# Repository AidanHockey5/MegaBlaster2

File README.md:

# Mega Blaster 2

Demo video can be found here: https://www.youtube.com/watch?v=4sKwGWfikdc

[Instruction Manual](https://github.com/AidanHockey5/MegaBlaster2/raw/master/man/MegaBlaster2InstructionManual.pdf)

[Store Link](https://www.aidanlawrence.com/product/mega-blaster-2/)

[Discord Link](https://discord.gg/M2skqkZhw2)

This project contains the source material for the Mega Blaster 2, a hardware Sega Genesis/Mega Drive video game music (VGM) player that utilizes the real sound chips. Play any Genesis track on-demand with brilliant sound quality on the actual YM2612/YM3438 and SN76489 PSG synthesizer chips that were found in the real Genesis consoles(1). The Mega Blaster 2 is compatible with both .vgm and .vgz files and can support both the YM2612 and YM3438 simply by changing the DIP switch values. This unit does not use any emulated sound - these are the real chips playing back logged data from the vgm files. 

# VGM Files

VGM files are logged datasets of the data that would have been sent to the real sound chips of whatever console or arcade machine was being sampled. The Mega Blaster 2 simply reads-in this data and sends it to the sound chips at the exact rate specified in the VGM spec, accurately recreating the original sound.

You can find Genesis VGM files here: https://project2612.org/list.php

You can find more VGM files here: https://vgmrips.net/packs/

Please make sure to remove any non-vgm/vgz files before adding them to your Mega Blaster 2's SD card, such as album art images, playlist files, and text files.

# VGM vs. VGZ

VGZ files are gzip compressed versions of VGM files. The Mega Blaster 2 is capable of automatically decompressing these vgz files on-the-fly at a slight performance penalty. If you'd like faster load times for each track, consider decompressing the VGZ files in advance by opening them with a program like [7zip](https://www.7-zip.org/)
The Mega Blaster 2 does not require file extensions in order to operate as it will verify files based on their internal headers.

# Building Your Own Unit

Here are some quick tips for building your own board.

1) You can find an interactive Bill of Materials (BOM) within the `schematic->bom` folder. Open the HTML file in any browser for an easy-to-use part position guide.
2) I use [KiCAD](https://kicad.org/) as my EDA suite.
4) I buy most of my components from [LCSC](https://lcsc.com/). I buy my PCBs from [JLCPCB](https://jlcpcb.com/). If you buy your PCBs from JLCPCB, you can often get a shipping discount on your LCSC parts order.
5) You will need an [Atmel ICE](https://www.microchip.com/DevelopmentTools/ProductDetails/ATATMEL-ICE) or [Jlink](https://www.segger.com/products/debug-probes/j-link/) to flash the bootloader. Once you have flashed the bootloader, all subsequent programming can be done via the on-board USB port. A cheaper option would be to grab a [Jlink EDU Mini](https://shop-us.segger.com/J_Link_EDU_mini_p/8.08.91.htm) as they feature the full functionality of a professional Jlink Unit with the stipulation that it is ONLY to be used for educational purposes. I personally use an Atmel ICE unit. You can find the bootloader bin file in the `bootloader` folder of the repository. [You can find an example of me programming the bootloader using Microchip Studio here.](https://youtu.be/FjPftGuLnGg?t=9259)
6) Once you've flashed the bootloader, you can drag the [.uf2 firmware file found on the releases page](https://github.com/AidanHockey5/MegaBlaster2/releases) on to the "drive" that pops up on your computer, or build from source. If you can't see any "drive," make sure the bootloader mentioned above is flashed correctly, then try double-tapping the RESET button. 
7) If your OS reports a USB fault, you may have a short somewhere on your USB IO lines, power lines, or your 32.768KHz crystal is not hooked up correctly.
8) I use [Visual Studio Code](https://code.visualstudio.com/) with the [PlatformIO](https://platformio.org/install/ide?install=vscode) extension.
9) Make sure your SN76489 PSG chip is orientated correctly. On this board, the PSG is upside-down relative to the rest of the board. The Flash IC is also upside-down. This was done for routing purposes. A small star on the silk-screen indicates the pin-1 position of every IC.
10) For general usage instructions, [please refer to the manual](https://github.com/AidanHockey5/MegaBlaster2/raw/master/man/MegaBlaster2InstructionManual.pdf).

# Reporting Bugs

As you can imagine, this is quite a complex project. There are bound to be bugs to squish, so if you happen to find any, [please report them over on the issues page](https://github.com/AidanHockey5/MegaBlaster2/issues) so I can tkae a look at them! Please try to document the steps it takes to recreate the bug if you happen to know them.

# Schematic

# License
The source code to this project is licensed under the AGPL 3.0 license.

The printed circuit board design files for the Mega Blaster 2, including it’s schematic, gerber files, KiCAD files, bill-of-materials, and 3D models are licensed under the Creative Commons Attribution-NonCommercial-ShareAlike 4.0 license.

You are permitted to build your own Mega Blaster 2 units for personal use. You are not permitted to sell said units.

(1) Pedantic note: Discrete YM2612 ICs were indeed included on some models of the Genesis, but the SN76489 PSG and YM3438 were found baked into ASIC chips on the actual consoles. The PSG's noise is slightly different on the ASIC version.

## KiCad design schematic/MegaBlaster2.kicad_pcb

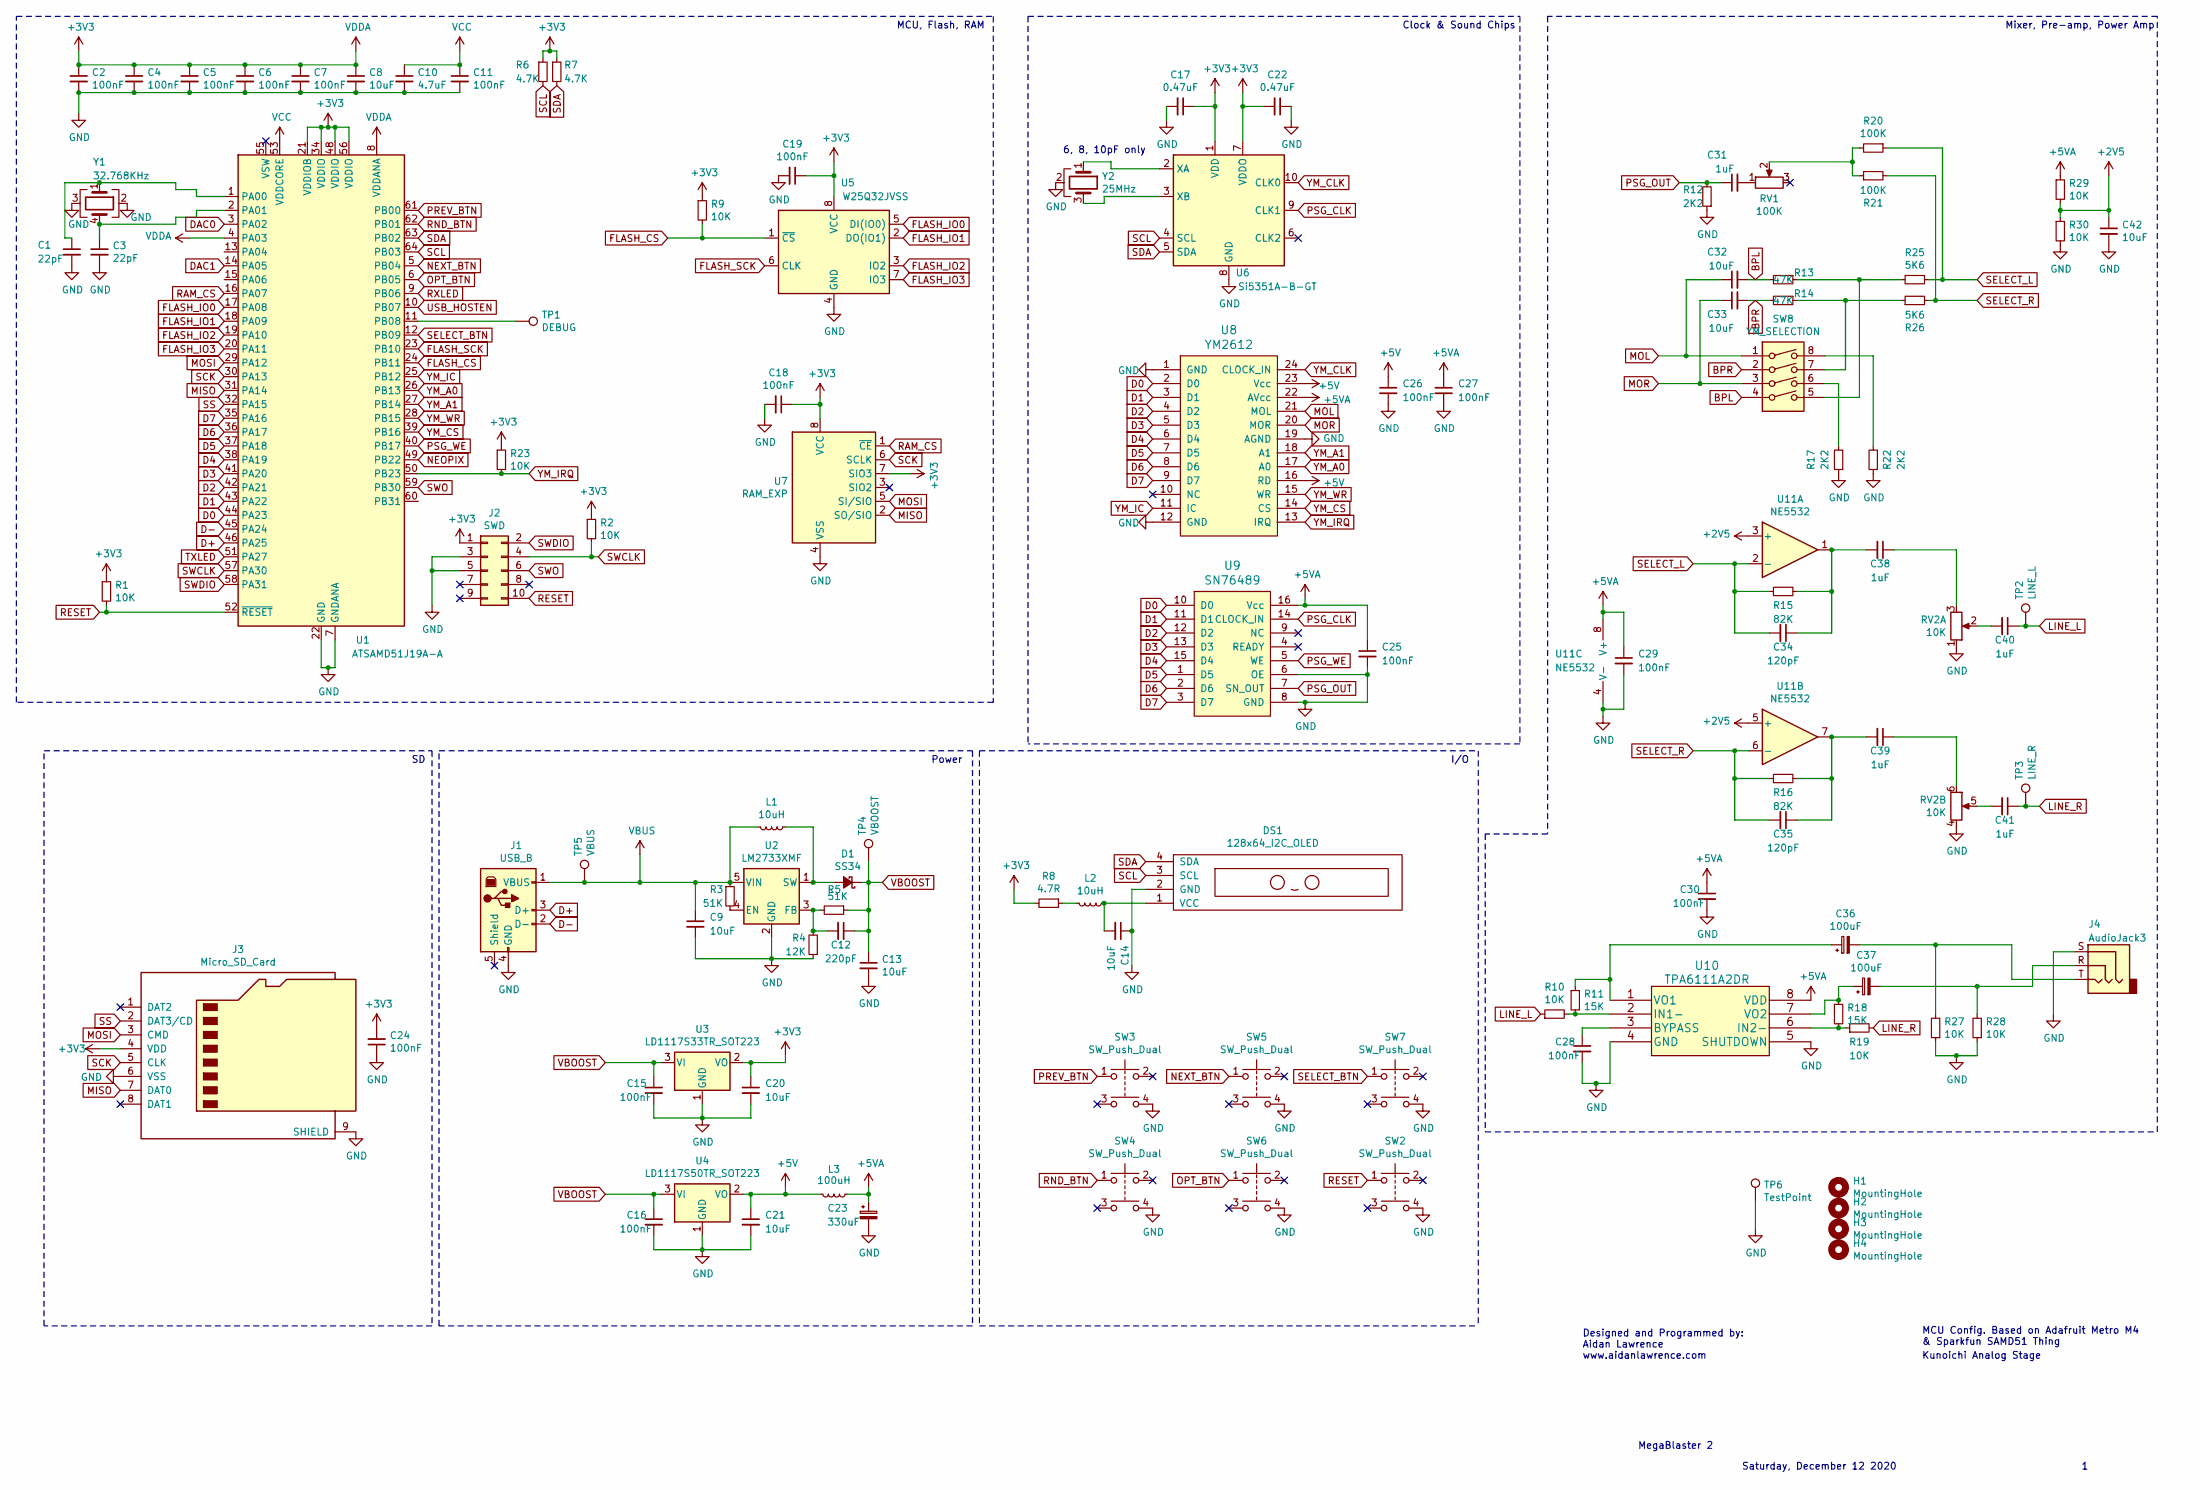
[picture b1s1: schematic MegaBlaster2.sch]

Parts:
C1, C3: 22pF; C_0603_1608Metric
C2, C4, C5, C6, C7, C11, C15, C16, C18, C19, C24, C25, C26, C27, C28, C29, C30: 100nF; C_0805_2012Metric
C8, C9, C13, C14, C20, C21, C32, C33, C42: 10uF; C_1206_3216Metric
C10: 4.7uF; C_0805_2012Metric
C12: 220pF; C_0603_1608Metric
C17, C22: 0.47uF; C_0805_2012Metric
C23: 330uF; CP_Elec_8x10
C31, C38, C39, C40, C41: 1uF; C_0805_2012Metric
C34, C35: 120pF; C_0603_1608Metric
C36, C37: 100uF; CP_Elec_6.3x7.7
D1: SS34; D_SMA
DS1: 128x64_I2C_OLED; oled_128x64
H1, H2, H3, H4: MountingHole; MountingHole_3.2mm_M3
J1: USB_B; USB_B_Lumberg_2411_02_Horizontal
J2: SWD; PinHeader_2x05_P1.27mm_Vertical
J3: Micro_SD_Card; SOFNG_TF_15x15_PUSH_PUSH
J4: AudioJack3; SWITCHCRAFT_35RAPC4BHN2
L1, L2: 10uH; L_4x4
L3: 100uH; 6x6Inductor
R1, R2, R9, R10, R19, R23, R27, R28, R29, R30: 10K; R_0805_2012Metric
R3, R5: 51K; R_0805_2012Metric
R4: 12K; R_0805_2012Metric
R6, R7: 4.7K; R_0805_2012Metric
R8: 4.7R; R_0805_2012Metric
R11, R18: 15K; R_0805_2012Metric
R12, R17, R22: 2K2; R_0805_2012Metric
R13, R14: 47K; R_0805_2012Metric
R15, R16: 82K; R_0805_2012Metric
R20, R21: 100K; R_0805_2012Metric
R25, R26: 5K6; R_0805_2012Metric
RV1: 100K; 3362P-1-103LF
RV2: 10K; Potentiometer_Alps_RK097_Dual_Horizontal
SW2, SW3, SW4, SW5, SW6, SW7: SW_Push_Dual; SW_TH_Tactile_Omron_B3F-10xx
SW8: YM_SELECTION; SW_DIP_SPSTx04_Slide_9.78x12.34mm_W7.62mm_P2.54mm
TP1: DEBUG; TestPoint_Pad_D2.0mm
TP2: LINE_L; TestPoint_Pad_D2.0mm
TP3: LINE_R; TestPoint_Pad_D2.0mm
TP4: VBOOST; TestPoint_Pad_D2.0mm
TP5: VBUS; TestPoint_Pad_D2.0mm
TP6: TestPoint; TestPoint_Pad_2.0x2.0mm
U1: ATSAMD51J19A-A; TQFP-64_10x10mm_P0.5mm
U2: LM2733XMF; SOT-23-5
U3: LD1117S33TR_SOT223; SOT-223-3_TabPin2
U4: LD1117S50TR_SOT223; SOT-223-3_TabPin2
U5: W25Q32JVSS; SOIC-8_5.23x5.23mm_P1.27mm
U6: Si5351A-B-GT; MSOP-10_3x3mm_P0.5mm
U7: RAM_EXP; SOIC-8_3.9x4.9mm_P1.27mm
U8: YM2612; DIP-24_W15.24mm_Socket
U9: SN76489; DIP-16_W7.62mm_Socket
U10: TPA6111A2DR; SOIC-8_3.9x4.9mm_P1.27mm
U11: NE5532; SOIC-8_3.9x4.9mm_P1.27mm
Y1: 32.768KHz; Crystal_SMD_SeikoEpson_MC306-4Pin_8.0x3.2mm
Y2: 25MHz; Crystal_SMD_3225-4Pin_3.2x2.5mm

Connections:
+2V5: C42.1, R29.2, R30.1, U11.3 (+), U11.5 (+)
+3V3: C2.1, C4.1, C5.1, C6.1, C7.1, C8.1, C17.1, C18.1, C19.1, C20.1, C22.2, C24.2, J2.1, J3.4 (VDD), R1.1, R2.1, R6.1, R7.1, R8.2, R9.1, R23.1, U1.4 (PA03), U1.8 (VDDANA), U1.21 (VDDIOB), U1.34 (VDDIO), U1.48 (VDDIO), U1.56 (VDDIO), U3.2 (VO), U5.8 (VCC), U6.1 (VDD), U6.7 (VDDO), U7.7 (SIO3), U7.8 (VCC)
+5V: C21.1, C26.1, L3.2, U4.2 (VO), U8.16 (RD), U8.23 (Vcc)
+5VA: C23.1, C25.1, C27.1, C29.1, C30.1, L3.1, R29.1, U8.22 (AVcc), U9.16 (Vcc), U10.8 (VDD), U11.8 (V+)
BPL: C32.2, R13.2, SW8.4
BPR: C33.2, R14.2, SW8.2
D0: U1.44 (PA23), U8.2 (D0), U9.10 (D0)
D1: U1.43 (PA22), U8.3 (D1), U9.11 (D1)
D2: U1.42 (PA21), U8.4 (D2), U9.12 (D2)
D3: U1.41 (PA20), U8.5 (D3), U9.13 (D3)
D4: U1.38 (PA19), U8.6 (D4), U9.15 (D4)
D5: U1.37 (PA18), U8.7 (D5), U9.1 (D5)
D6: U1.36 (PA17), U8.8 (D6), U9.2 (D6)
D7: U1.35 (PA16), U8.9 (D7), U9.3 (D7)
D+: J1.3 (D+), U1.46 (PA25)
D-: J1.2 (D-), U1.45 (PA24)
DAC0: U1.3 (PA02)
DAC1: U1.14 (PA05)
FLASH_CS: R9.2, U1.24 (PB11), U5.1 (~CS)
FLASH_IO0: U1.17 (PA08), U5.5 (DI(IO0))
FLASH_IO1: U1.18 (PA09), U5.2 (DO(IO1))
FLASH_IO2: U1.19 (PA10), U5.3 (IO2)
FLASH_IO3: U1.20 (PA11), U5.7 (IO3)
FLASH_SCK: U1.23 (PB10), U5.6 (CLK)
GND: C1.2, C2.2, C3.2, C4.2, C5.2, C6.2, C7.2, C8.2, C9.2, C10.2, C11.2, C13.2, C14.1, C15.2, C16.2, C17.2, C18.2, C19.2, C20.2, C21.2, C22.1, C23.2, C24.1, C25.2, C26.2, C27.2, C28.2, C29.2, C30.2, C42.2, DS1.2 (GND), J1.4 (GND), J2.3, J2.5, J3.6 (VSS), J3.9 (SHIELD), J4.S, R4.1, R12.1, R17.1, R22.1, R27.1, R28.1, R30.2, RV2.1 (6), RV2.4, SW2.4, SW3.4, SW4.4, SW5.4, SW6.4, SW7.4, TP6.1, U1.7 (GNDANA), U1.22 (GND), U1.33 (GND), U1.47 (GND), U1.54 (GND), U2.2 (GND), U3.1 (GND), U4.1 (GND), U5.4 (GND), U6.8 (GND), U7.4 (VSS), U8.1 (GND), U8.12 (GND), U8.19 (AGND), U9.6 (OE), U9.8 (GND), U10.4 (GND), U10.5 (SHUTDOWN), U11.4 (V-), Y1.2, Y1.3, Y2.2
LINE_L: C40.1, R10.1, TP2.1
LINE_R: C41.1, R19.2, TP3.1
MISO: J3.7 (DAT0), U1.31 (PA14), U7.2 (SO/SIO)
MOL: C32.1, SW8.1, U8.21 (MOL)
MOR: C33.1, SW8.3, U8.20 (MOR)
MOSI: J3.3 (CMD), U1.29 (PA12), U7.5 (SI/SIO)
NEOPIX: U1.49 (PB22)
NEXT_BTN: SW5.1, U1.5 (PB04)
unnamed: C1.1, U1.1 (PA00), Y1.1
unnamed: C3.1, U1.2 (PA01), Y1.4
unnamed: C12.2, R4.2, R5.2, U2.3 (FB)
unnamed: C14.2, DS1.1 (VCC), L2.1
unnamed: C28.1, U10.3 (BYPASS)
unnamed: C31.2, RV1.1
unnamed: C34.1, C38.2, R15.2, U11.1
unnamed: C35.1, C39.2, R16.2, U11.7
unnamed: C36.1, R11.1, U10.1 (VO1)
unnamed: C36.2, J4.T, R27.2
unnamed: C37.1, R18.1, U10.7 (VO2)
unnamed: C37.2, J4.R, R28.2
unnamed: C38.1, RV2.3 (4)
unnamed: C39.1, RV2.6
unnamed: C40.2, RV2.2
unnamed: C41.2, RV2.5
unnamed: D1.2 (A), L1.1, U2.1 (SW)
unnamed: L2.2, R8.1
unnamed: R3.2, U2.4 (EN)
unnamed: R10.2, R11.2, U10.2 (IN1-)
unnamed: R13.1, R25.2, SW8.5
unnamed: R14.1, R26.1, SW8.7
unnamed: R17.2, SW8.6
unnamed: R18.2, R19.1, U10.6 (IN2-)
unnamed: R20.2, R21.1, RV1.2
unnamed: R22.2, SW8.8
unnamed: TP1.1, U1.11 (PB08)
unnamed: U6.2 (XA), Y2.1
unnamed: U6.3 (XB), Y2.3
OPT_BTN: SW6.1, U1.6 (PB05)
PREV_BTN: SW3.1, U1.61 (PB00)
PSG_CLK: U6.9 (CLK1), U9.14 (CLOCK_IN)
PSG_OUT: C31.1, R12.2, U9.7 (SN_OUT)
PSG_WE: U1.40 (PB17), U9.5 (WE)
RAM_CS: U1.16 (PA07), U7.1 (~CE)
RESET: J2.10, R1.2, SW2.1, U1.52 (~RESET)
RND_BTN: SW4.1, U1.62 (PB01)
RXLED: U1.9 (PB06)
SCK: J3.5 (CLK), U1.30 (PA13), U7.6 (SCLK)
SCL: DS1.3 (SCL), R6.2, U1.64 (PB03), U6.4 (SCL)
SDA: DS1.4 (SDA), R7.2, U1.63 (PB02), U6.5 (SDA)
SELECT_BTN: SW7.1, U1.12 (PB09)
SELECT_L: C34.2, R15.1, R20.1, R25.1, U11.2 (-)
SELECT_R: C35.2, R16.1, R21.2, R26.2, U11.6 (-)
SS: J3.2 (DAT3/CD), U1.32 (PA15)
SWCLK: J2.4, R2.2, U1.57 (PA30)
SWDIO: J2.2, U1.58 (PA31)
SWO: J2.6, U1.59 (PB30)
TXLED: U1.51 (PA27)
USB_HOSTEN: U1.10 (PB07)
VBOOST: C12.1, C13.1, C15.1, C16.1, D1.1 (K), R5.1, TP4.1, U3.3 (VI), U4.3 (VI)
VBUS: C9.1, J1.1 (VBUS), L1.2, R3.1, TP5.1, U2.5 (VIN)
VCC: C10.1, C11.1, U1.53 (VDDCORE)
YM_A0: U1.26 (PB13), U8.17 (A0)
YM_A1: U1.27 (PB14), U8.18 (A1)
YM_CLK: U6.10 (CLK0), U8.24 (CLOCK_IN)
YM_CS: U1.39 (PB16), U8.14 (CS)
YM_IC: U1.25 (PB12), U8.11 (IC)
YM_IRQ: R23.2, U1.50 (PB23), U8.13 (IRQ)
YM_WR: U1.28 (PB15), U8.15 (WR)

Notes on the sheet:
Designed and Programmed by: Aidan Lawrence www.aidanlawrence.com
MCU Config. Based on Adafruit Metro M4 & Sparkfun SAMD51 Thing
MegaBlaster 2
Saturday, December 12 2020
6, 8, 10pF only
Kunoichi Analog Stage
MCU, Flash, RAM
Clock & Sound Chips
Mixer, Pre-amp, Power Amp
I/O
Power

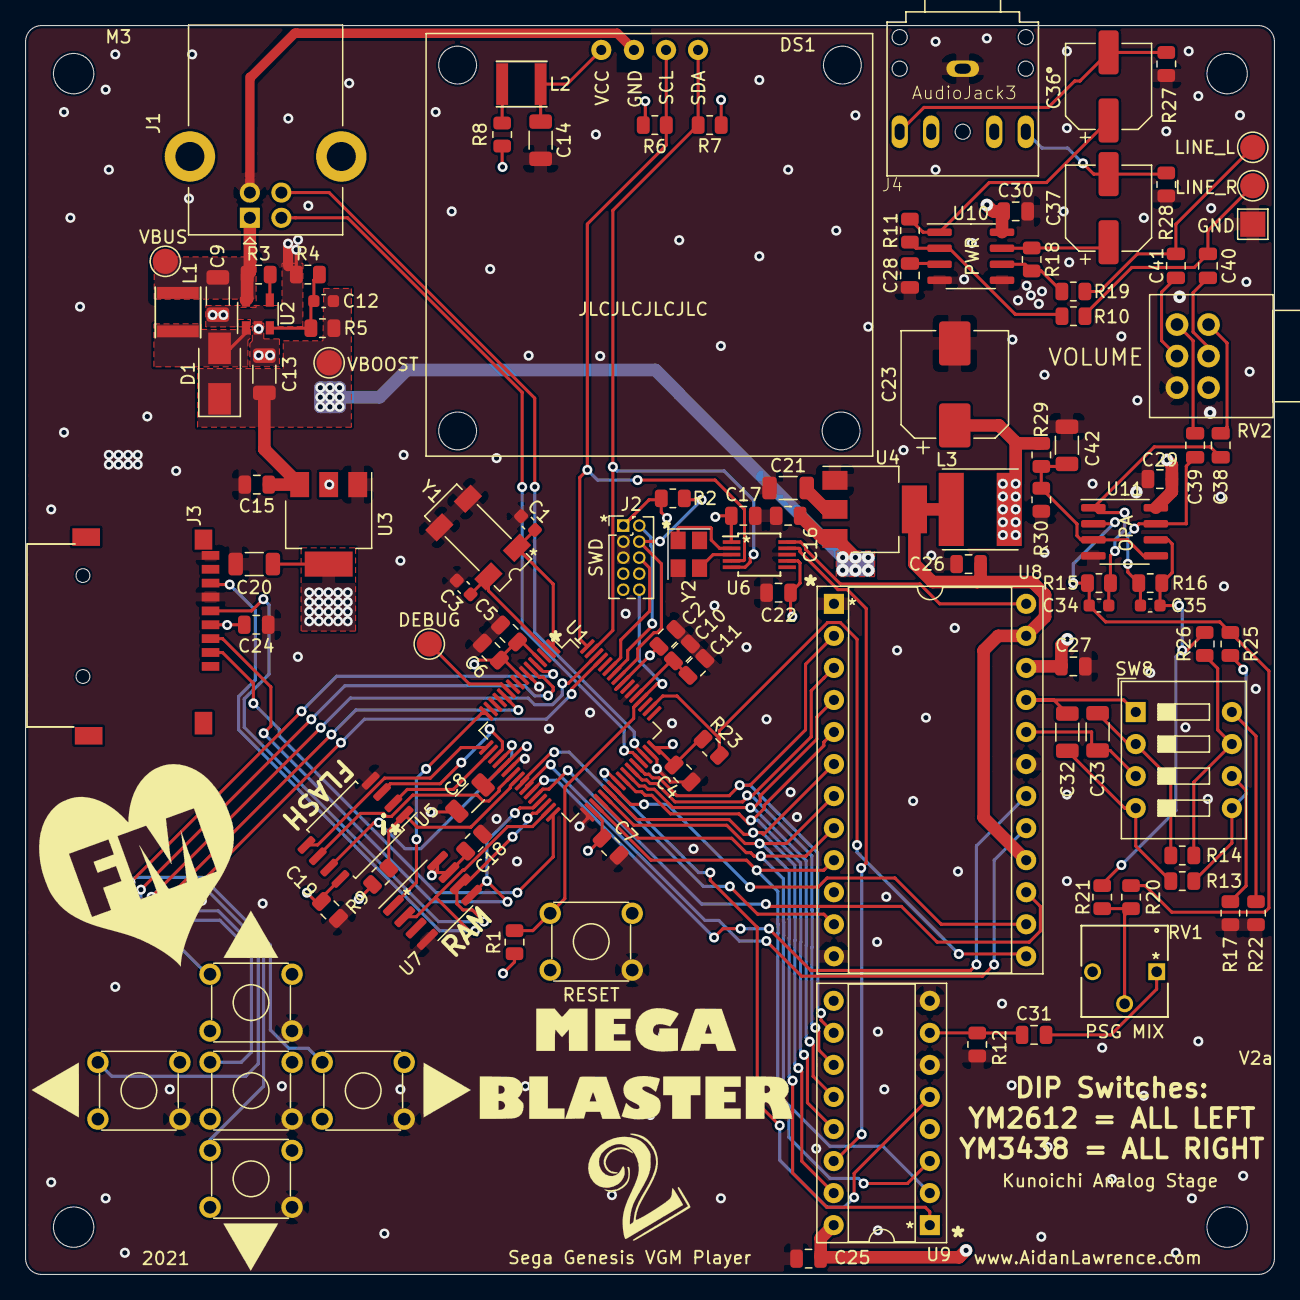
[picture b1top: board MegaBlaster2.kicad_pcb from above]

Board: 4 copper layers, 99.0 x 99.0 mm, 112 parts (0 on the bottom side), 87 nets.

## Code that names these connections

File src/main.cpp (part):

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bool isOledOn = true;

//Buttons
const int prev_btn = 47;    //PORT_PB00;
const int down_btn = 48;    //PORT_PB01;
const int next_btn = 49;    //PORT_PB04;
const int up_btn = 50;  //PORT_PB05;
const int select_btn = 19;  //PORT_PB09;
Bounce buttons[5];

//Counters
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  u8g2.clearDisplay();

  //SD
  REG_PORT_DIRSET0 = PORT_PA15; //Set PA15 to output
  if(!SD.begin(PORT_PA15, SPI_FULL_SPEED))
  {
    Serial.println("SD Mount Failed!");
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  //Direct IO examples for reading pins
  //if (REG_PORT_IN0 & PORT_PA19)  // if (digitalRead(12) == HIGH)
  //if (!(REG_PORT_IN0 | ~PORT_PA19)) // if (digitalRead(12) == LOW) FOR NON-PULLED PINS!
  //if(!(REG_PORT_IN1 & next_btn)) //LOW for PULLED PINS

  // //Group 1 is port B, PINCFG just wants the literal pin number on the port, DIRCLR and OUTSET want the masked PORT_XX00 *not* the PIN_XX00
  // //Prev button input pullup
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
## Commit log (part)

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2020-12-21 Init
2020-12-22 Routing
2020-12-23 Board v1 complete
2021-01-07 Porting player
2021-01-07 Programmed buttons
2021-01-07 Added true RNG system for rand select seed
2021-01-07 Menu lib, neopixel removed from pcb, bootloader
2021-01-07 silkscreen update
2021-01-08 New ARM-optimized bus write algo
2021-01-08 New chip timings
2021-01-09 File manifest system
2021-01-09 merge
2021-01-10 Adding Menu System
2021-01-10 save
2021-01-11 custom board config
2021-01-11 buttons
2021-01-11 Debounced buttons
2021-01-12 Fix U8G2 and index root
2021-01-13 VGM UI
2021-01-13 dir file indexing
2021-01-13 NEXT button IN_ORDER
2021-01-14 Fixed manifest rebuild
2021-01-14 new index counter
2021-01-14 getDirIndices function finished
2021-01-15 Random file history
2021-01-16 Playmode selector
2021-01-17 dir index from full path and root shuffle bugs fixed
2021-01-17 Added loop modifier
2021-01-17 Lock loop edit element if LOOP playback option is selected
2021-01-17 IRQ self test
2021-01-17 Option to disable IRQ Test
2021-01-18 PCB Update
2021-01-20 DAC Stream early prototype
2021-01-22 Less stupid way of setting dac stream ready flags lol
2021-01-25 paged RAM stores
2021-01-26 chunk-streaming PCM storage for external RAM
2021-01-28 DAC Streams now have basic support
2021-01-29 VGZ Decompress
2021-01-30 Added invalid file warning screen
2021-01-31 Toggle one-off loop menu toggle
2021-01-31 Increase gzip buf and fix root file picking
2021-01-31 Manifest verify function
2021-02-01 Added Uf2 converter
2021-02-07 Manual
2021-02-08 Manual rev 1
2021-02-11 New logo
2021-02-21 Revise Instruction Manual
    * Fixed some minor grammar
    * Improved readability slightly (see comparison doc attached in comments)
    * Added PDF bookmarks by Word Headers option
    * Added hyperlink to www.aidanlawrence.com in first page
    * fixed some spelling, punctuation, and capitalization of software and hardware names
    * added mild disclaimer about ground loop isolators (they very often have low-pass filters and can affect audio quality, especially ones made for car stereo systems)
2021-02-23 Schematic cleanup
2021-02-23 add lic
2021-02-23 Create LICENSE
2021-03-09 Min limit on loop adjust set to 1 from 0
2021-03-10 Added missing libs
2021-03-10 Added missing clock lib
2021-03-11 slowly removing manifest system
2021-03-11 fixing random history
2021-03-11 Full SD Shuffle ALL
2021-03-12 First version of player without manifest system
2021-03-12 Fixed in-order seek on root and remove meta files upon entering dir
2021-03-12 Removed manifest file system
2021-03-12 Check for _SYS dir on startup
2021-03-12 Commented-out serial debugging lines
2021-03-13 SdFat patch to prevent sequetial, matching subsstring dirs from conflicting
2021-03-15 minor check for crazy gd3 offsets
2021-03-16 manual update
2021-03-16 Add discord link
2021-03-20 block ym2612 test reg writes
2021-04-16 Fixed shuffle bug and file order bug
2021-05-14 Automatic SI5351A configuration
2021-09-15 Added channel control for each chip
2021-09-17 Changed wording on ch muting interface to be a bit more intuitive
2021-10-08 Fixed call to true-rng for shuffled playlists
2021-10-08 RNG inclusivity/exclusivity fix
2021-10-11 Fixed issue with DAC streams
2022-01-20 Added sync-tone function
2022-02-01 PSG low-byte fix
2022-02-01 YM channel muting fixed
2025-01-27 Reset sample counter upon first VGM wait period

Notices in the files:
parts and their libraries:
Copyright 2016 Accelerated Designs. All rights reserved.
